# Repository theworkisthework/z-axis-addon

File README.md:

Released under an MIT licence, no warranty implied or given, use at own risk etc etc.

This adds a Z-axis using a TMC2130 stepper motor. It connects to the ESP32 Plotter Controller via the aux ports (I2C & SPI).

It also provides a connection to the Stallgaurd output for endstop detection.

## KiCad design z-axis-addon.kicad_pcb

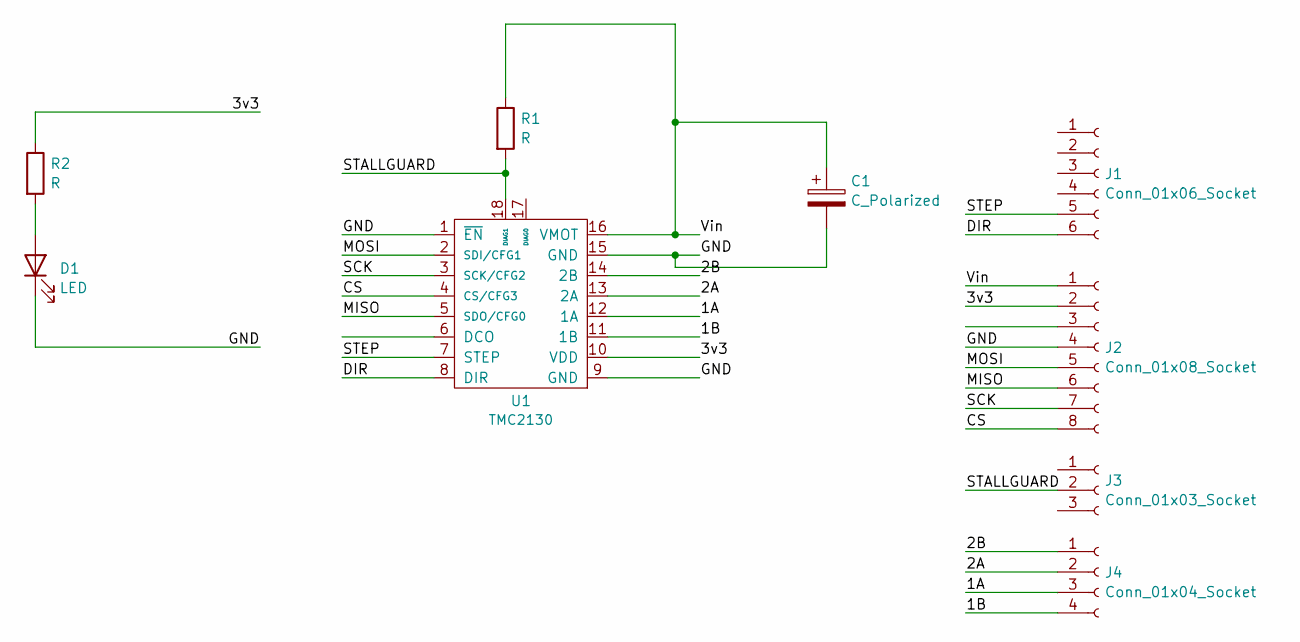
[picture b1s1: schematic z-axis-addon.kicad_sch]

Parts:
C1: C_Polarized; CP_Elec_6.3x5.7
D1: LED
J1: Conn_01x06_Socket; JST_PH_S6B-PH-K_1x06_P2.00mm_Horizontal
J2: Conn_01x08_Socket; JST_PH_S8B-PH-K_1x08_P2.00mm_Horizontal
J3: Conn_01x03_Socket; JST_PH_S3B-PH-K_1x03_P2.00mm_Horizontal
J4: Conn_01x04_Socket; JST_PH_S4B-PH-K_1x04_P2.00mm_Horizontal
R1: R; R_0805_2012Metric
R2: R
U1: TMC2130; StepstickTMCv2

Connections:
/1A: J4.3, U1.12 (1A)
/1B: J4.4, U1.11 (1B)
/2A: J4.2, U1.13 (2A)
/2B: J4.1, U1.14 (2B)
/3v3: J2.2, R2.1, U1.10 (VDD)
/CS: J2.8, U1.4 (CS/CFG3)
/DIR: J1.6, U1.8 (DIR)
/GND: C1.2, D1.1 (K), J2.4, U1.1 (~EN), U1.9 (GND), U1.15 (GND)
/MISO: J2.6, U1.5 (SDO/CFG0)
/MOSI: J2.5, U1.2 (SDI/CFG1)
/SCK: J2.7, U1.3 (SCK/CFG2)
/STALLGUARD: J3.2, R1.2, U1.18 (DIAG1)
/STEP: J1.5, U1.7 (STEP)
/Vin: C1.1, J2.1, R1.1, U1.16 (VMOT)
unnamed: D1.2 (A), R2.2

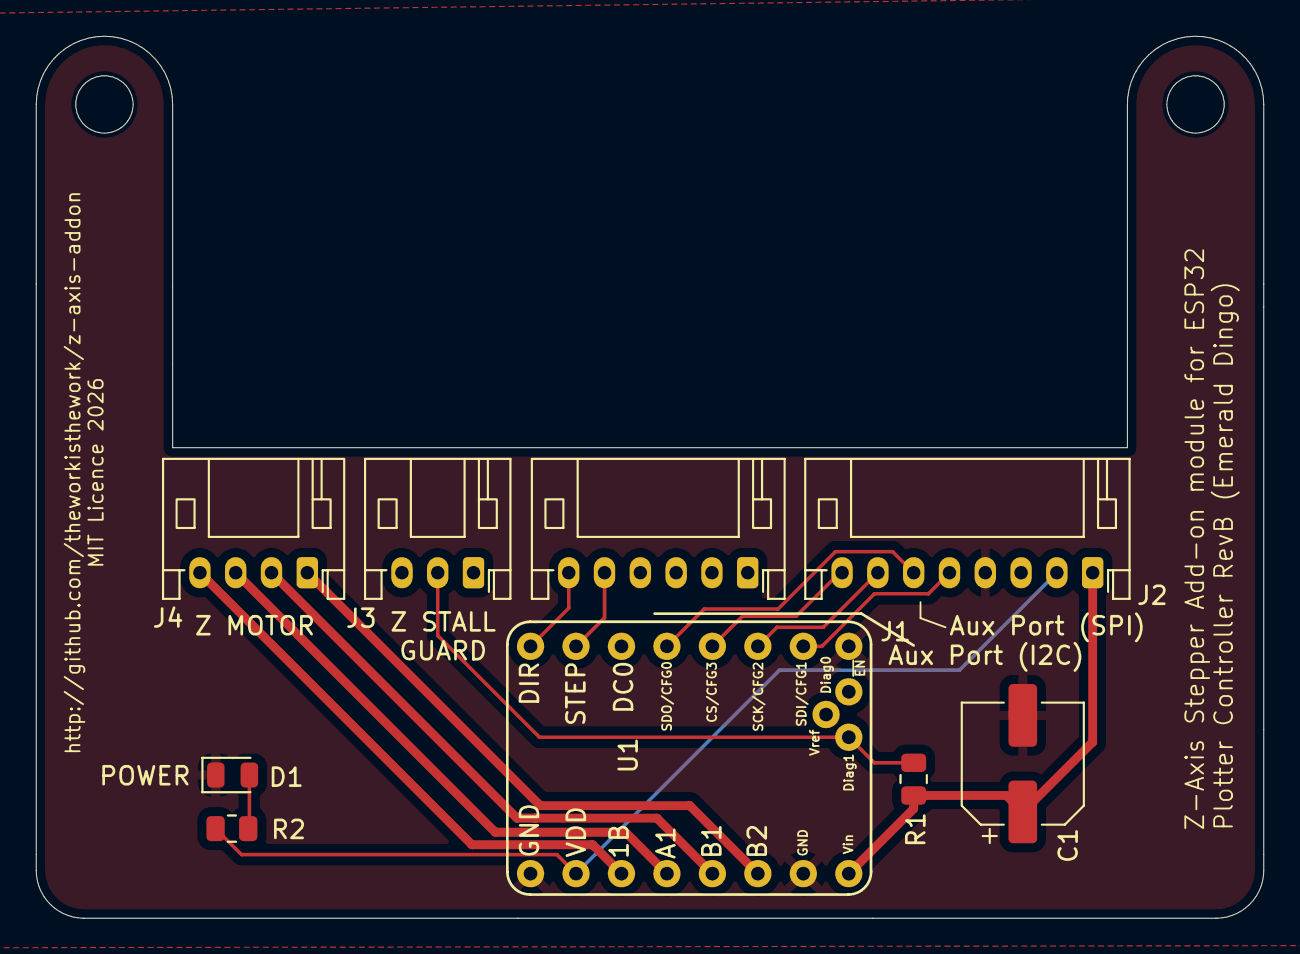
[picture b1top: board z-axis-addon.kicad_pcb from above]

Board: 2 copper layers, 68.6 x 49.3 mm, 11 parts (0 on the bottom side), 15 nets.

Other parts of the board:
H3, H4: MountingHole_3.2mm_M3

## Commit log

2026-02-21 Update text on PCB
2026-02-21 Add readme and render of board
2026-02-21 Add production files
2026-02-21 Add link to ESP32 Plotter Controller in README
2026-02-21 Update for production output directory
2026-02-21 Add visualization and 3d model (step)
2026-02-21 Fix typo in url
2026-02-21 Update schematic to include power led

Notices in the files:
z-axis-addon.kicad_pcb:
MIT Licence 2026
